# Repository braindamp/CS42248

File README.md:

# CS42248
I can't get this working just yet

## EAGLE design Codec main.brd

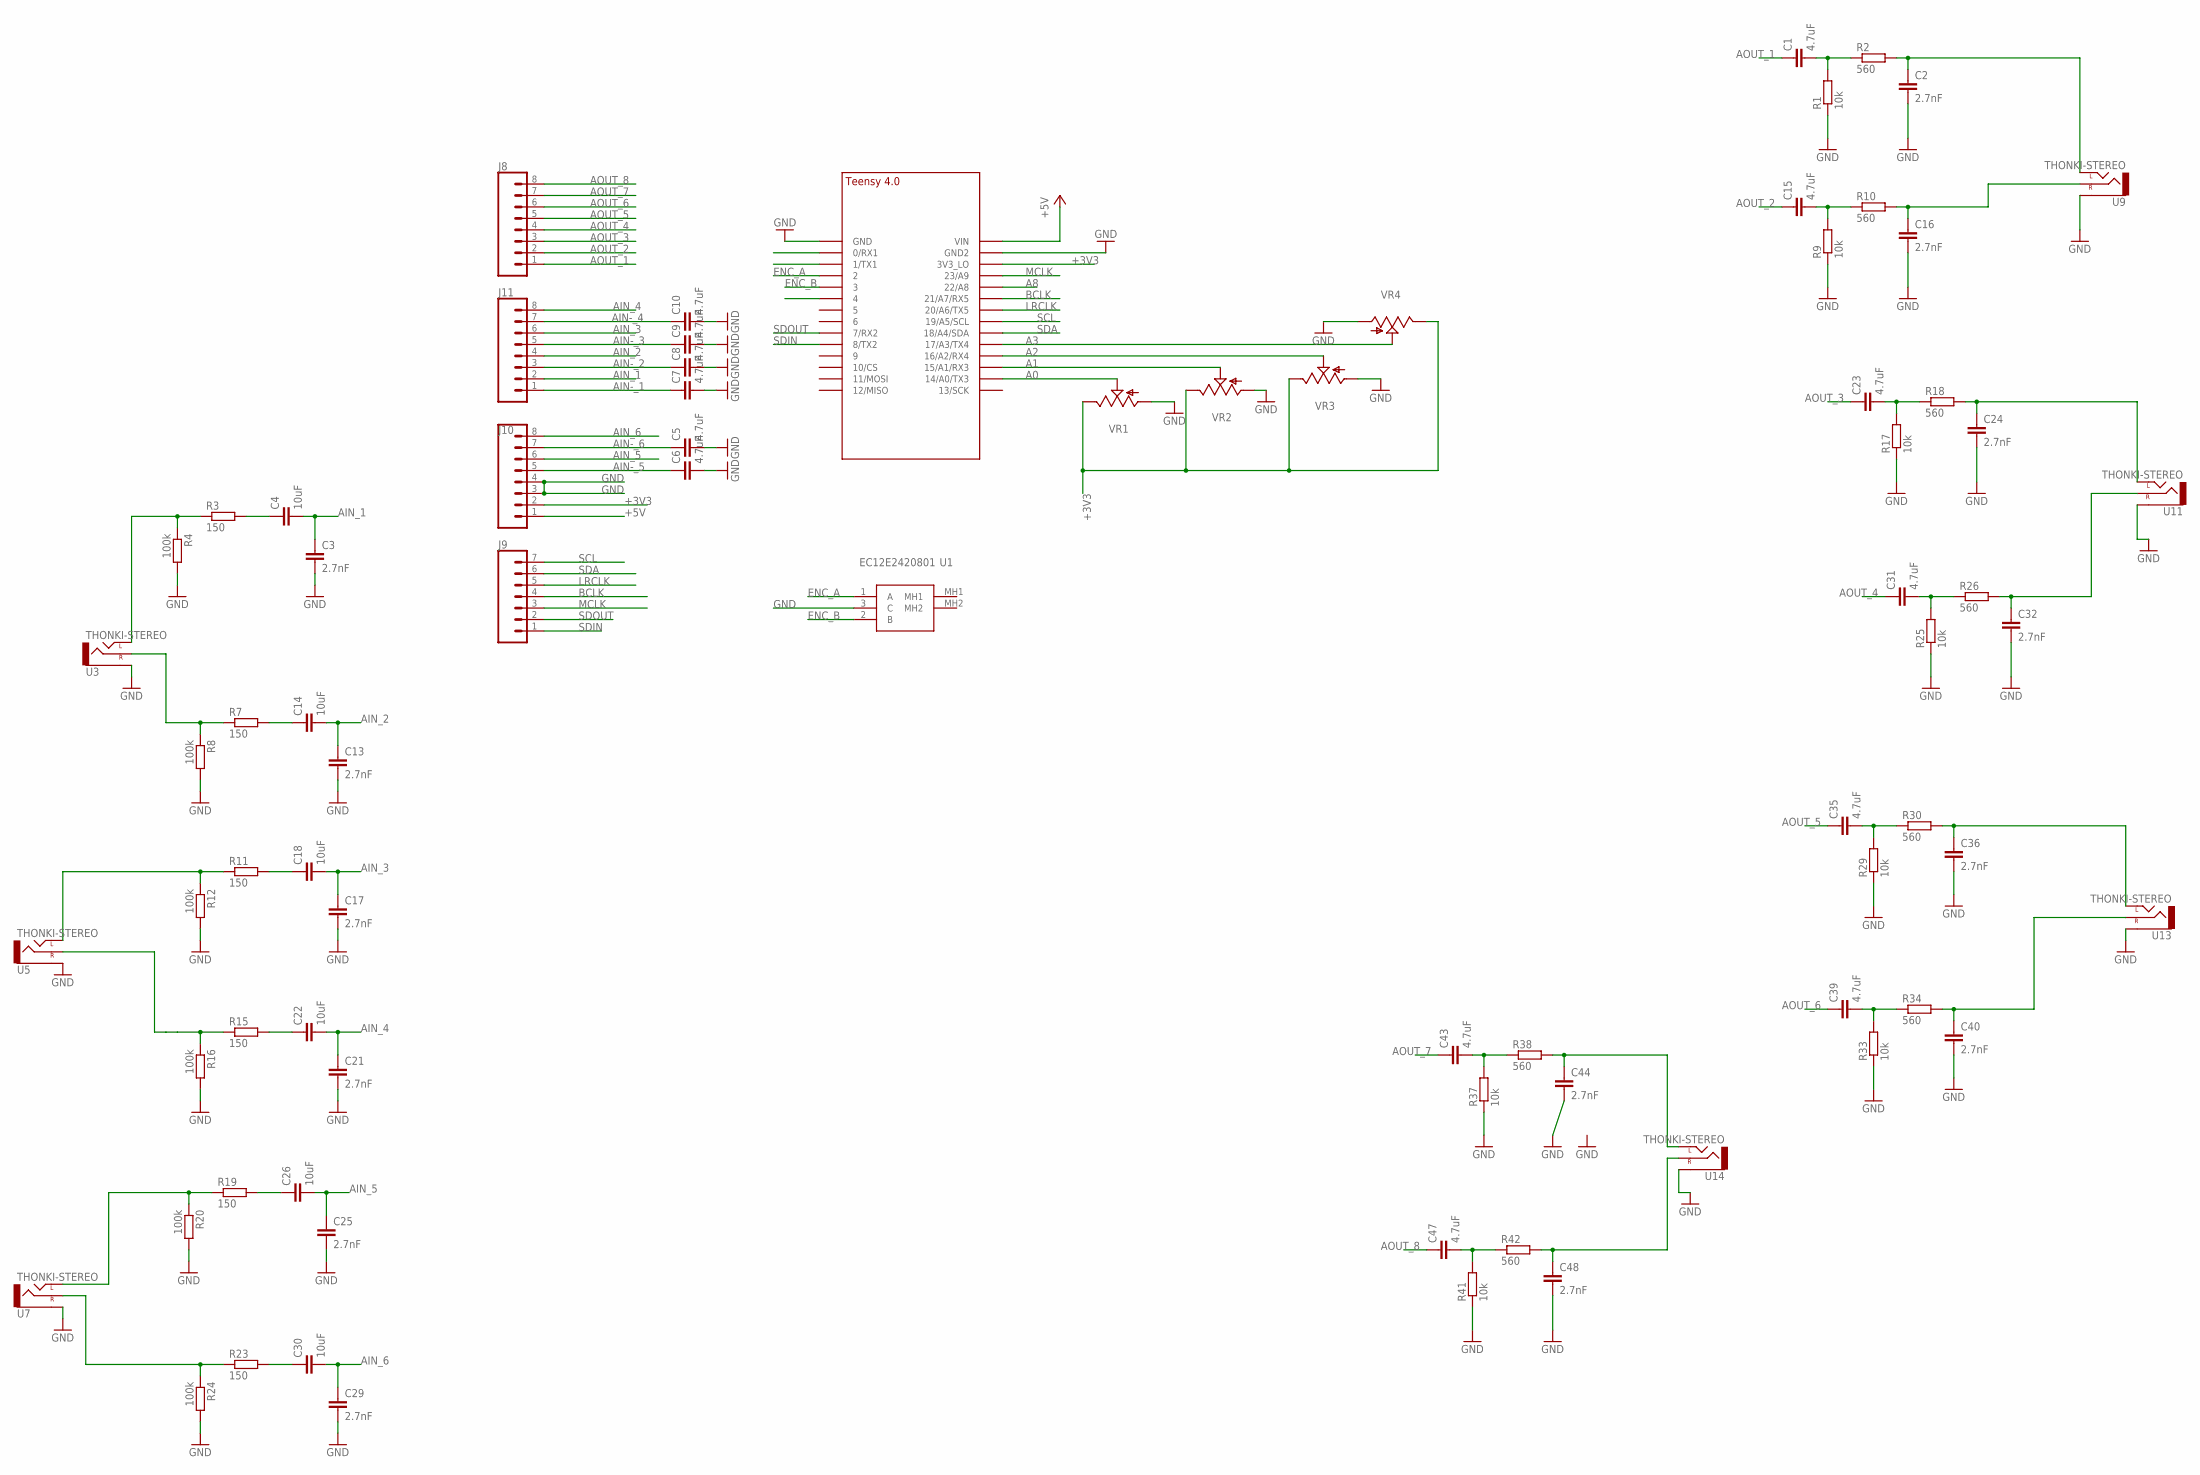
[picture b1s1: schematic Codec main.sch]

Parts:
C1, C5, C6, C7, C8, C9, C10, C15, C23, C31, C35, C39, C43, C47: 4.7uF; C0805
C2, C3, C13, C16, C17, C21, C24, C25, C29, C32, C36, C40, C44, C48: 2.7nF; C0805
C4, C14, C18, C22, C26, C30: 10uF; C0805
J8, J10, J11: CONN_08"; 1X08
J9: CONN_07; 1X07
R1, R9, R17, R25, R29, R33, R37, R41: 10k; R0603
R2, R10, R18, R26, R30, R34, R38, R42: 560; M0805
R3, R7, R11, R15, R19, R23: 150; M0805
R4, R8, R12, R16, R20, R24: 100k; R0603
U1: EC12E2420801
U3, U5, U7, U9, U11, U13, U14: THONKI-STEREO; WQP-PJ366ST_JACK
U$1: TEENSY_4.0
VR1, VR2, VR3, VR4: 9MM_SNAP-IN_POT_; 9MM_SNAP-IN_POT

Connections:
+3V3: J10.2, U$1.3V3_LO, VR1.3 (E), VR2.3 (E), VR3.3 (E), VR4.3 (E)
+5V: J10.1, U$1.VIN
A0: U$1.14/A0 (14/A0/TX3), VR1.2 (S)
A1: U$1.15/A1 (15/A1/RX3), VR2.2 (S)
A2: U$1.16/A2 (16/A2/RX4), VR3.2 (S)
A3: U$1.17/A3 (17/A3/TX4), VR4.2 (S)
A8: U$1.22/A8
AIN-_1: C7.1, J11.1
AIN-_2: C8.1, J11.3
AIN-_3: C9.1, J11.5
AIN-_4: C10.1, J11.7
AIN-_5: C6.1, J10.5
AIN-_6: C5.1, J10.7
AIN_1: C3.1, C4.2, J11.2
AIN_2: C13.1, C14.2, J11.4
AIN_3: C17.1, C18.2, J11.6
AIN_4: C21.1, C22.2, J11.8
AIN_5: C25.1, C26.2, J10.6
AIN_6: C29.1, C30.2, J10.8
AOUT_1: C1.1, J8.1
AOUT_2: C15.1, J8.2
AOUT_3: C23.1, J8.3
AOUT_4: C31.1, J8.4
AOUT_5: C35.1, J8.5
AOUT_6: C39.1, J8.6
AOUT_7: C43.1, J8.7
AOUT_8: C47.1, J8.8
BCLK: J9.4, U$1.21/A7 (21/A7/RX5)
ENC_A: U1.1 (A), U$1.2
ENC_B: U1.2 (B), U$1.3/CANTX (3)
GND: C2.2, C3.2, C5.2, C6.2, C7.2, C8.2, C9.2, C10.2, C13.2, C16.2, C17.2, C21.2, C24.2, C25.2, C29.2, C32.2, C36.2, C40.2, C44.2, C48.2, J10.3, J10.4, R1.1, R4.2, R8.2, R9.1, R12.2, R16.2, R17.1, R20.2, R24.2, R25.1, R29.1, R33.1, R37.1, R41.1, U1.3 (C), U3.P$3_SLEEVE (SLEEVE), U5.P$3_SLEEVE (SLEEVE), U7.P$3_SLEEVE (SLEEVE), U9.P$3_SLEEVE (SLEEVE), U11.P$3_SLEEVE (SLEEVE), U13.P$3_SLEEVE (SLEEVE), U14.P$3_SLEEVE (SLEEVE), U$1.GND, U$1.GND2, VR1.1 (A), VR2.1 (A), VR3.1 (A), VR4.1 (A)
LRCLK: J9.5, U$1.20/A6 (20/A6/TX5)
MCLK: J9.3, U$1.23/A9
unnamed: C1.2, R1.2, R2.1
unnamed: C2.1, R2.2, U9.P$1_TIP (LEFT)
unnamed: C4.1, R3.2
unnamed: R7.1, R8.1, U3.P$2_SWITCH (RIGHT)
unnamed: C14.1, R7.2
unnamed: C15.2, R9.2, R10.1
unnamed: R3.1, R4.1, U3.P$1_TIP (LEFT)
unnamed: C16.1, R10.2, U9.P$2_SWITCH (RIGHT)
unnamed: R11.1, R12.1, U5.P$1_TIP (LEFT)
unnamed: C18.1, R11.2
unnamed: R15.1, R16.1, U5.P$2_SWITCH (RIGHT)
unnamed: C22.1, R15.2
unnamed: C23.2, R17.2, R18.1
unnamed: C24.1, R18.2, U11.P$1_TIP (LEFT)
unnamed: R19.1, R20.1, U7.P$1_TIP (LEFT)
unnamed: C26.1, R19.2
unnamed: R23.1, R24.1, U7.P$2_SWITCH (RIGHT)
unnamed: C30.1, R23.2
unnamed: C31.2, R25.2, R26.1
unnamed: C32.1, R26.2, U11.P$2_SWITCH (RIGHT)
unnamed: C35.2, R29.2, R30.1
unnamed: C36.1, R30.2, U13.P$1_TIP (LEFT)
unnamed: C39.2, R33.2, R34.1
unnamed: C40.1, R34.2, U13.P$2_SWITCH (RIGHT)
unnamed: C43.2, R37.2, R38.1
unnamed: C44.1, R38.2, U14.P$1_TIP (LEFT)
unnamed: C47.2, R41.2, R42.1
unnamed: C48.1, R42.2, U14.P$2_SWITCH (RIGHT)
SCL: J9.7, U$1.19/A5/SCL
SDA: J9.6, U$1.18/A4/SDA
SDIN: J9.1, U$1.8 (8/TX2)
SDOUT: J9.2, U$1.7 (7/RX2)

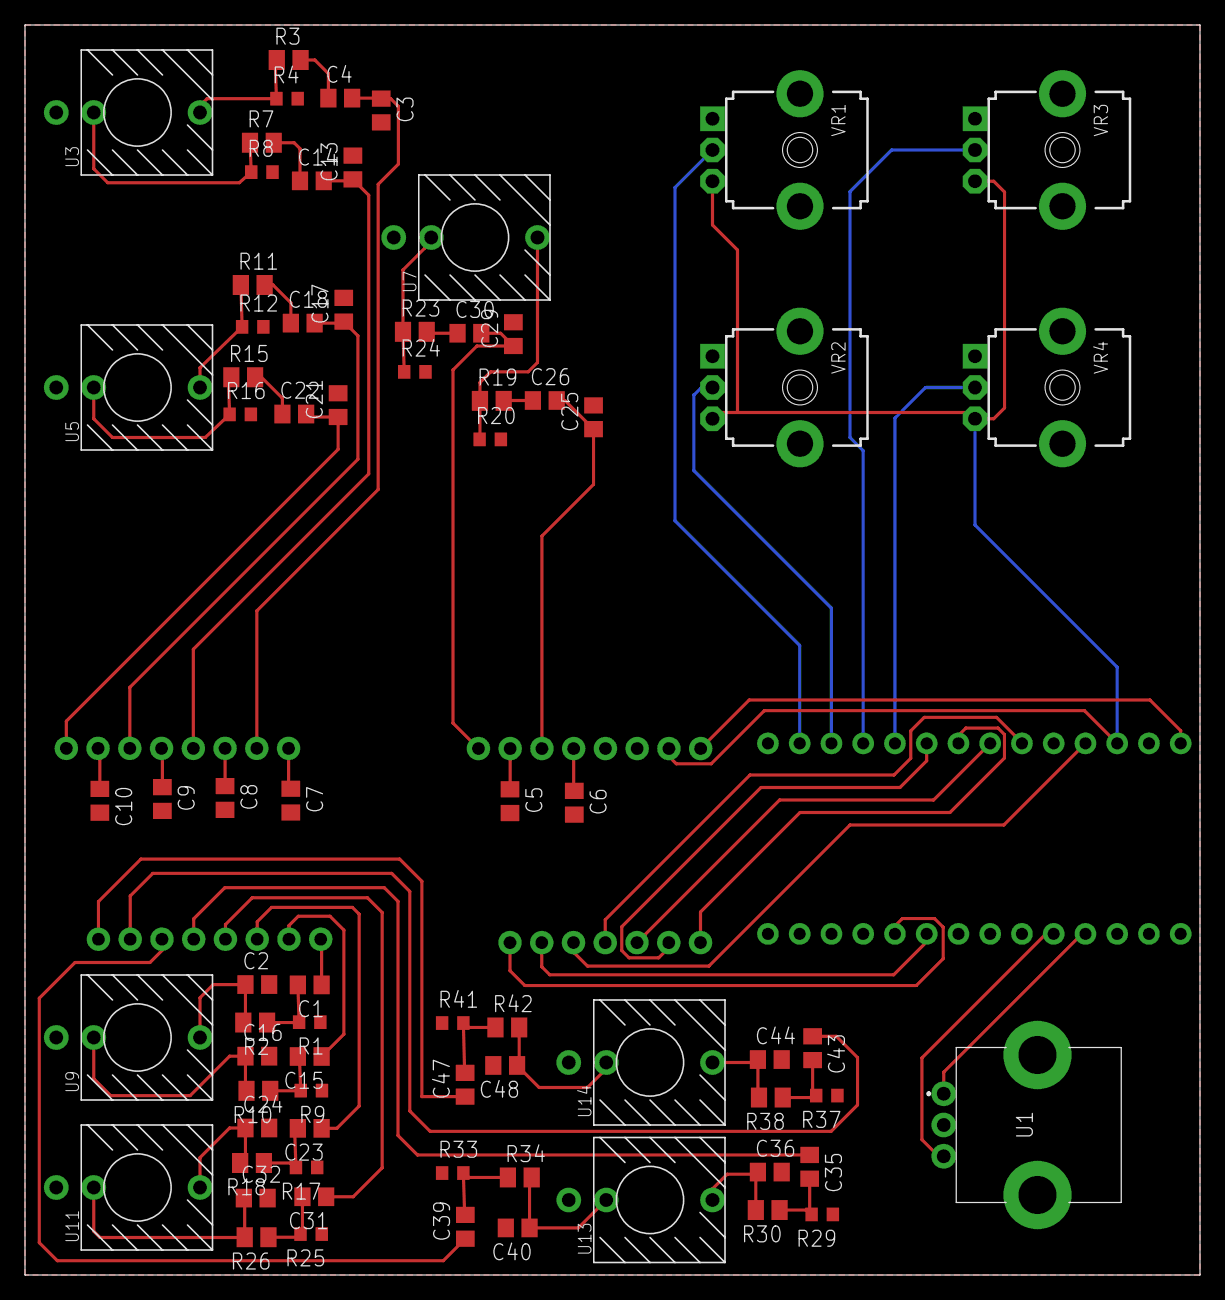
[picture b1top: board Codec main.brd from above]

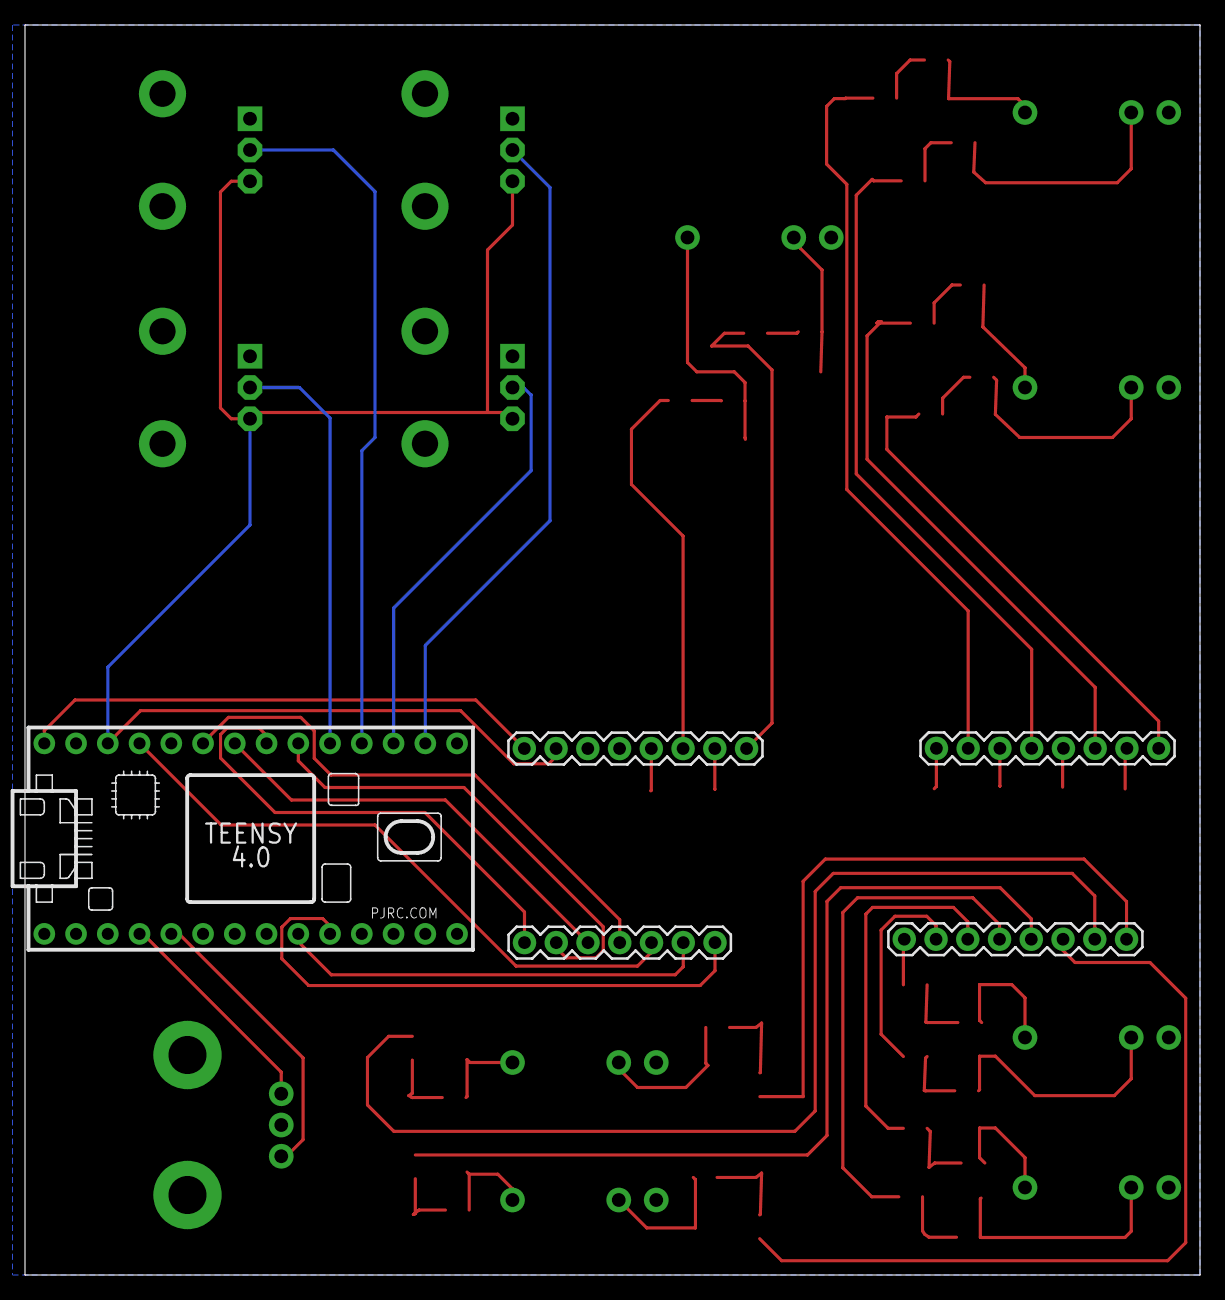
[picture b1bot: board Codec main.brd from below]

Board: 2 copper layers, 94.0 x 100.0 mm, 79 parts (5 on the bottom side), 64 nets.

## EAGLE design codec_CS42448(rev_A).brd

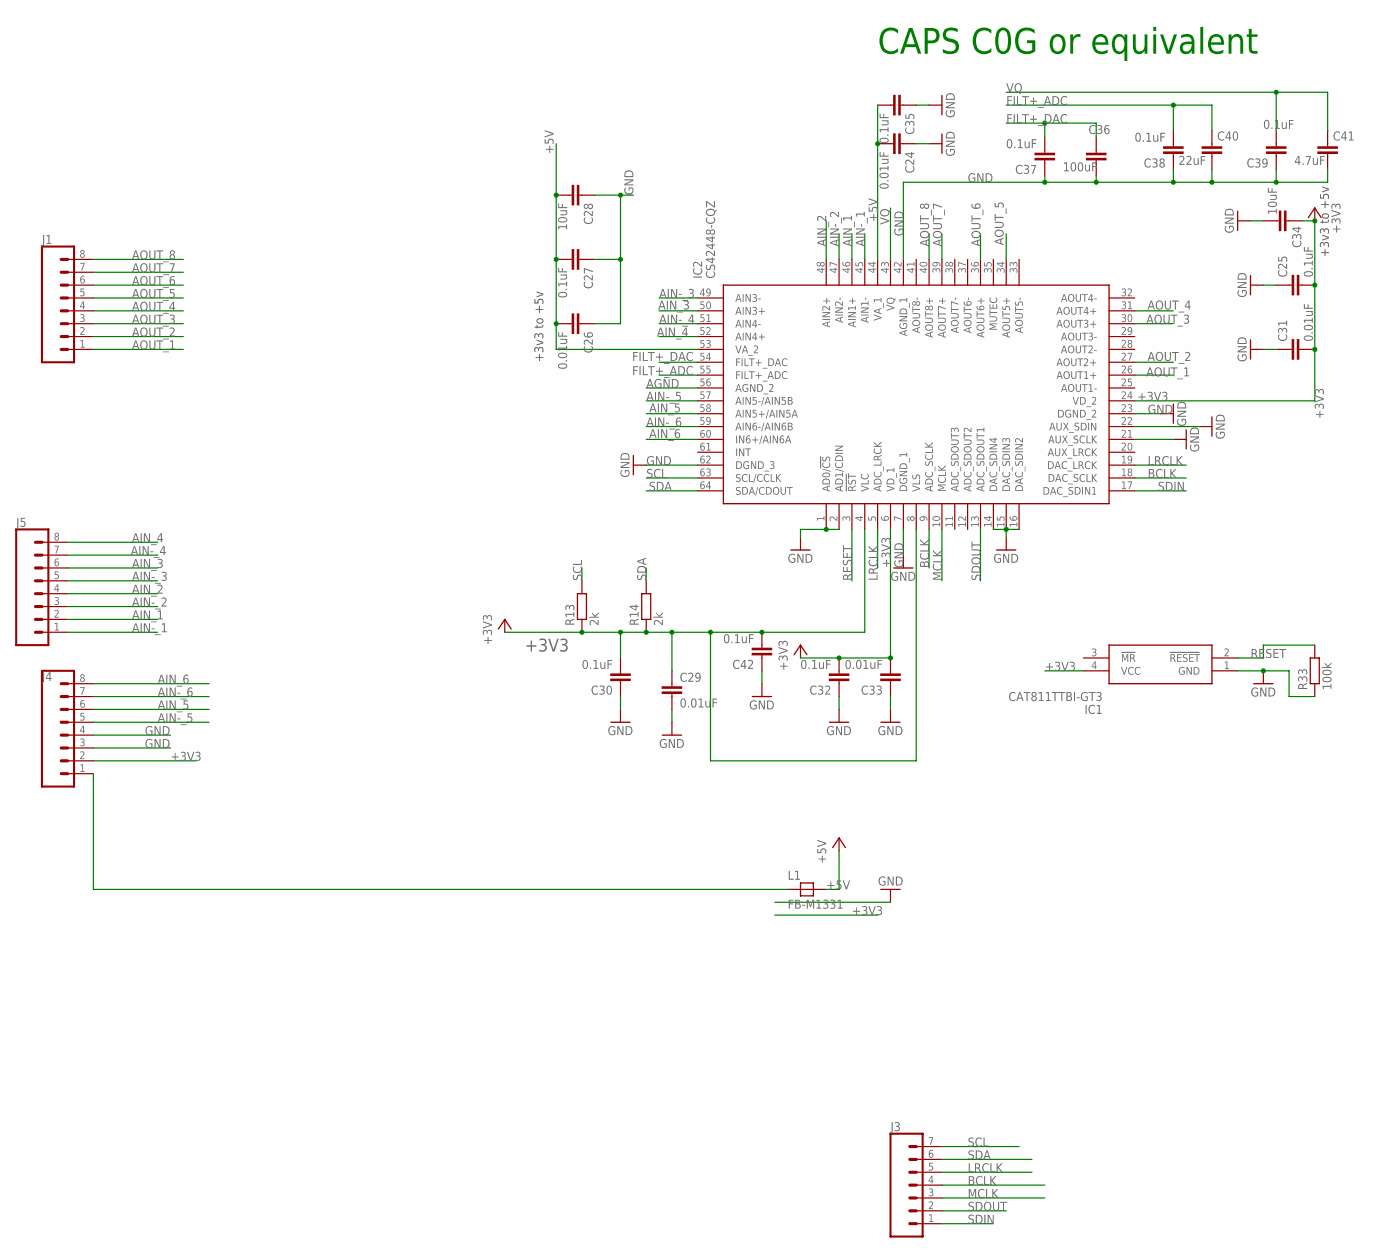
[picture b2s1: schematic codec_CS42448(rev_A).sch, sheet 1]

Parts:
C24, C26, C29, C31, C33: 0.01uF; C0805
C25, C27, C30, C32, C35, C37, C38, C39: 0.1uF; C0603
C28, C34: 10uF; C0805
C36: 100uF; C1206
C40: 22uF; C0805
C41: 4.7uF; C0805
C42: 0.1uF; C0805
IC1: CAT811TTBI-GT3; 4-PIN-SOT-143(BI-SUFFIX-CASE-5
IC2: CS42448-CQZ; QFP50P1200X1200X160-64N
J1, J4, J5: CONN_08"; 1X08
J3: CONN_07; 1X07
L1: FB-M1331; M1331
R13, R14: 2k; R0603
R33: 100k; R0603

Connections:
+3V3: C25.2, C29.1, C30.2, C31.2, C32.2, C33.2, C34.1, C42.2, IC1.4 (VCC), IC2.4 (VLC), IC2.6 (VD_1), IC2.8 (VLS), IC2.24 (VD_2), J4.2, R13.1, R14.1
+5V: C24.2, C26.2, C27.2, C28.2, C35.2, IC2.44 (VA_1), IC2.53 (VA_2), L1.2
AGND: IC2.56 (AGND_2)
AIN-_1: IC2.45 (AIN1-), J5.1
AIN-_2: IC2.47 (AIN2-), J5.3
AIN-_3: IC2.49 (AIN3-), J5.5
AIN-_4: IC2.51 (AIN4-), J5.7
AIN-_5: IC2.57 (AIN5-/AIN5B), J4.5
AIN-_6: IC2.59 (AIN6-/AIN6B), J4.7
AIN_1: IC2.46 (AIN1+), J5.2
AIN_2: IC2.48 (AIN2+), J5.4
AIN_3: IC2.50 (AIN3+), J5.6
AIN_4: IC2.52 (AIN4+), J5.8
AIN_5: IC2.58 (AIN5+/AIN5A), J4.6
AIN_6: IC2.60 (IN6+/AIN6A), J4.8
AOUT_1: IC2.26 (AOUT1+), J1.1
AOUT_2: IC2.27 (AOUT2+), J1.2
AOUT_3: IC2.30 (AOUT3+), J1.3
AOUT_4: IC2.31 (AOUT4+), J1.4
AOUT_5: IC2.34 (AOUT5+), J1.5
AOUT_6: IC2.36 (AOUT6+), J1.6
AOUT_7: IC2.39 (AOUT7+), J1.7
AOUT_8: IC2.40 (AOUT8+), J1.8
BCLK: IC2.9 (ADC_SCLK), IC2.18 (DAC_SCLK), J3.4
FILT+_ADC: C38.2, C40.1, IC2.55 (FILT+_ADC)
FILT+_DAC: C36.1, C37.2, IC2.54 (FILT+_DAC)
GND: C24.1, C25.1, C26.1, C27.1, C28.1, C29.2, C30.1, C31.1, C32.1, C33.1, C34.2, C35.1, C36.2, C37.1, C38.1, C39.1, C40.2, C41.2, C42.1, IC1.1 (GND), IC2.1 (AD0/!CS), IC2.2 (AD1/CDIN), IC2.7 (DGND_1), IC2.14 (DAC_SDIN4), IC2.15 (DAC_SDIN3), IC2.16 (DAC_SDIN2), IC2.21 (AUX_SCLK), IC2.22 (AUX_SDIN), IC2.23 (DGND_2), IC2.42 (AGND_1), IC2.62 (DGND_3), J4.3, J4.4, R33.1
LRCLK: IC2.5 (ADC_LRCK), IC2.19 (DAC_LRCK), J3.5
MCLK: IC2.10 (MCLK), J3.3
unnamed: J4.1, L1.1
RESET: IC1.2 (!RESET), IC2.3 (!RST), R33.2
SCL: IC2.63 (SCL/CCLK), J3.7, R13.2
SDA: IC2.64 (SDA/CDOUT), J3.6, R14.2
SDIN: IC2.17 (DAC_SDIN1), J3.1
SDOUT: IC2.13 (ADC_SDOUT1), J3.2
VQ: C39.2, C41.1, IC2.43 (VQ)

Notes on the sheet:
+3v3 to +5v
CAPS C0G or equivalent

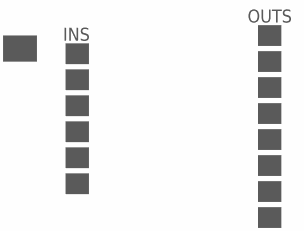
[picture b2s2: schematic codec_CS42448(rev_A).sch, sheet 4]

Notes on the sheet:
INS
OUTS

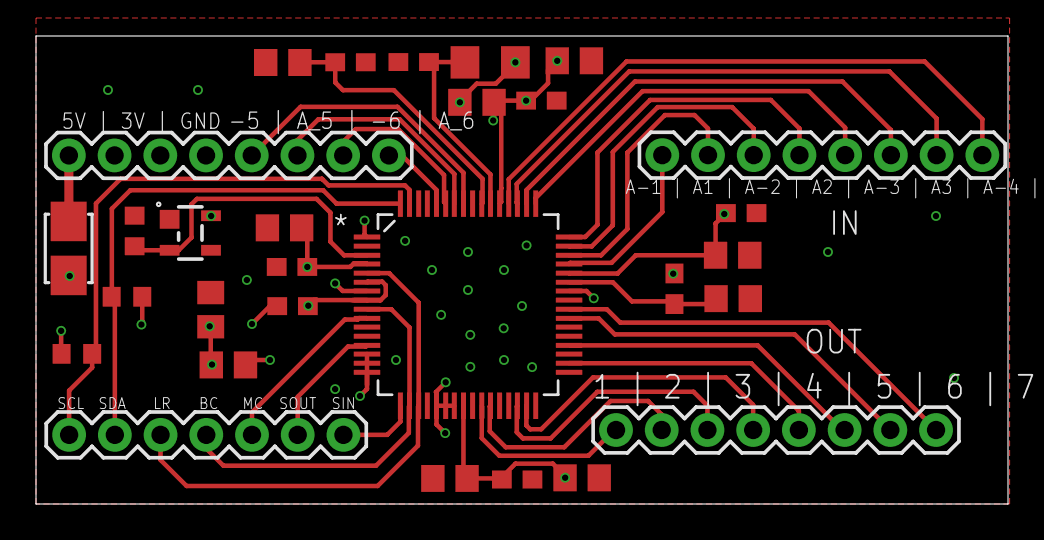
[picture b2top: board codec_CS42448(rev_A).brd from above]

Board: 4 copper layers, 54.0 x 26.0 mm, 29 parts (0 on the bottom side), 35 nets.

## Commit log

2022-03-14 Add files via upload
    I can't verify if these work yet.
    Codec main is the board housing Teensy 4 and Codec_CS42448 is the board with codec on.

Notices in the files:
parts and their libraries:
SparkFun-Connectors: Licensing: Creative Commons ShareAlike 4.0 International - https://creativecommons.org/licenses/by-sa/4.0
